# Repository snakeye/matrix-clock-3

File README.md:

# LED Matrix Clock v3

## Overview
Imagine combining the charm of retro LED displays with modern smart technology. **LED Matrix Clock v3** is a creative DIY project that transforms five 8x8 LED matrices into a sleek timepiece. Powered by an ESP8266 microcontroller, this clock not only displays the current time but also keeps it accurate by syncing with an NTP server. The DS3231 RTC module ensures reliability, while automatic daylight saving adjustments make it smarter than your average clock. Built using the Arduino framework and developed in the PlatformIO environment, this project is a perfect blend of classic aesthetics and cutting-edge convenience.

## Features
- **Time Display**: Shows the current time in the local time zone.
- **Automatic Daylight Calculation**: Adjusts for daylight saving time automatically.
- **NTP Synchronization**: Regular updates to the RTC clock via NTP ensure time accuracy.
- **Automatic Brightness**: The display brightness is adjusted according to ambient lighting.

## Hardware Requirements
- **ESP8266 (ESP-12 Module)**
- **5 x 8x8 LED Matrices using MAX7219 drivers**
- **DS3231 RTC Module**

## Software Requirements
- **PlatformIO** (installed via Python Pipenv)
- **Arduino Framework**
- **Python 3.x**

## Installation Instructions

### 1. Clone the Repository
```bash
git clone https://github.com/snakeye/matrix-clock-3.git
cd matrix-clock-3
```

### 3. Set Up the Environment
Ensure you have **Python 3.x** installed. Use Pipenv to install PlatformIO and set up the environment:
```bash
pip install pipenv
pipenv install --dev
pipenv shell
```
This command will install PlatformIO and any additional dependencies needed for the project.

### 2. Configure WiFi Connection
Before building the firmware, set up your WiFi connection:
1. Locate the file `src/config.cpp.example` in the repository.
2. Rename the file to `src/config.cpp`:
   ```bash
   mv src/config.cpp.example src/config.cpp
   ```
3. Open `src/config.cpp` in a text editor and update the placeholders with your WiFi network name (SSID) and password:
   ```cpp
   const char* ssid = "YourNetworkName";
   const char* password = "YourNetworkPassword";
   ```

### 4. Build the Firmware
Use the following command within the Pipenv shell to build the firmware:
```bash
platformio run
```

### 5. Upload the Firmware
Ensure your ESP8266 is connected via USB, and upload the firmware using:
```bash
platformio run --target upload
```
Following updates can be performed using OTA. Discover devices' IP address and run the following command:
```bash
platformio run --target upload --upload-port 192.168.1.179
```

## Usage
Once the firmware is uploaded, the clock will start running and display the current time. It will automatically adjust for daylight saving time and periodically synchronize with an NTP server.

## Troubleshooting
- Ensure your ESP8266 module is properly connected and powered.
- If the upload fails, check the USB connection and the selected upload port in `platformio.ini`.
- Verify your Wi-Fi credentials are correctly configured in the `src/config.cpp` file.

## License
This project is licensed under the MIT License. See the LICENSE file for more details.

## Contributions
Contributions are welcome! Please fork the repository and create a pull request with your improvements or fixes.

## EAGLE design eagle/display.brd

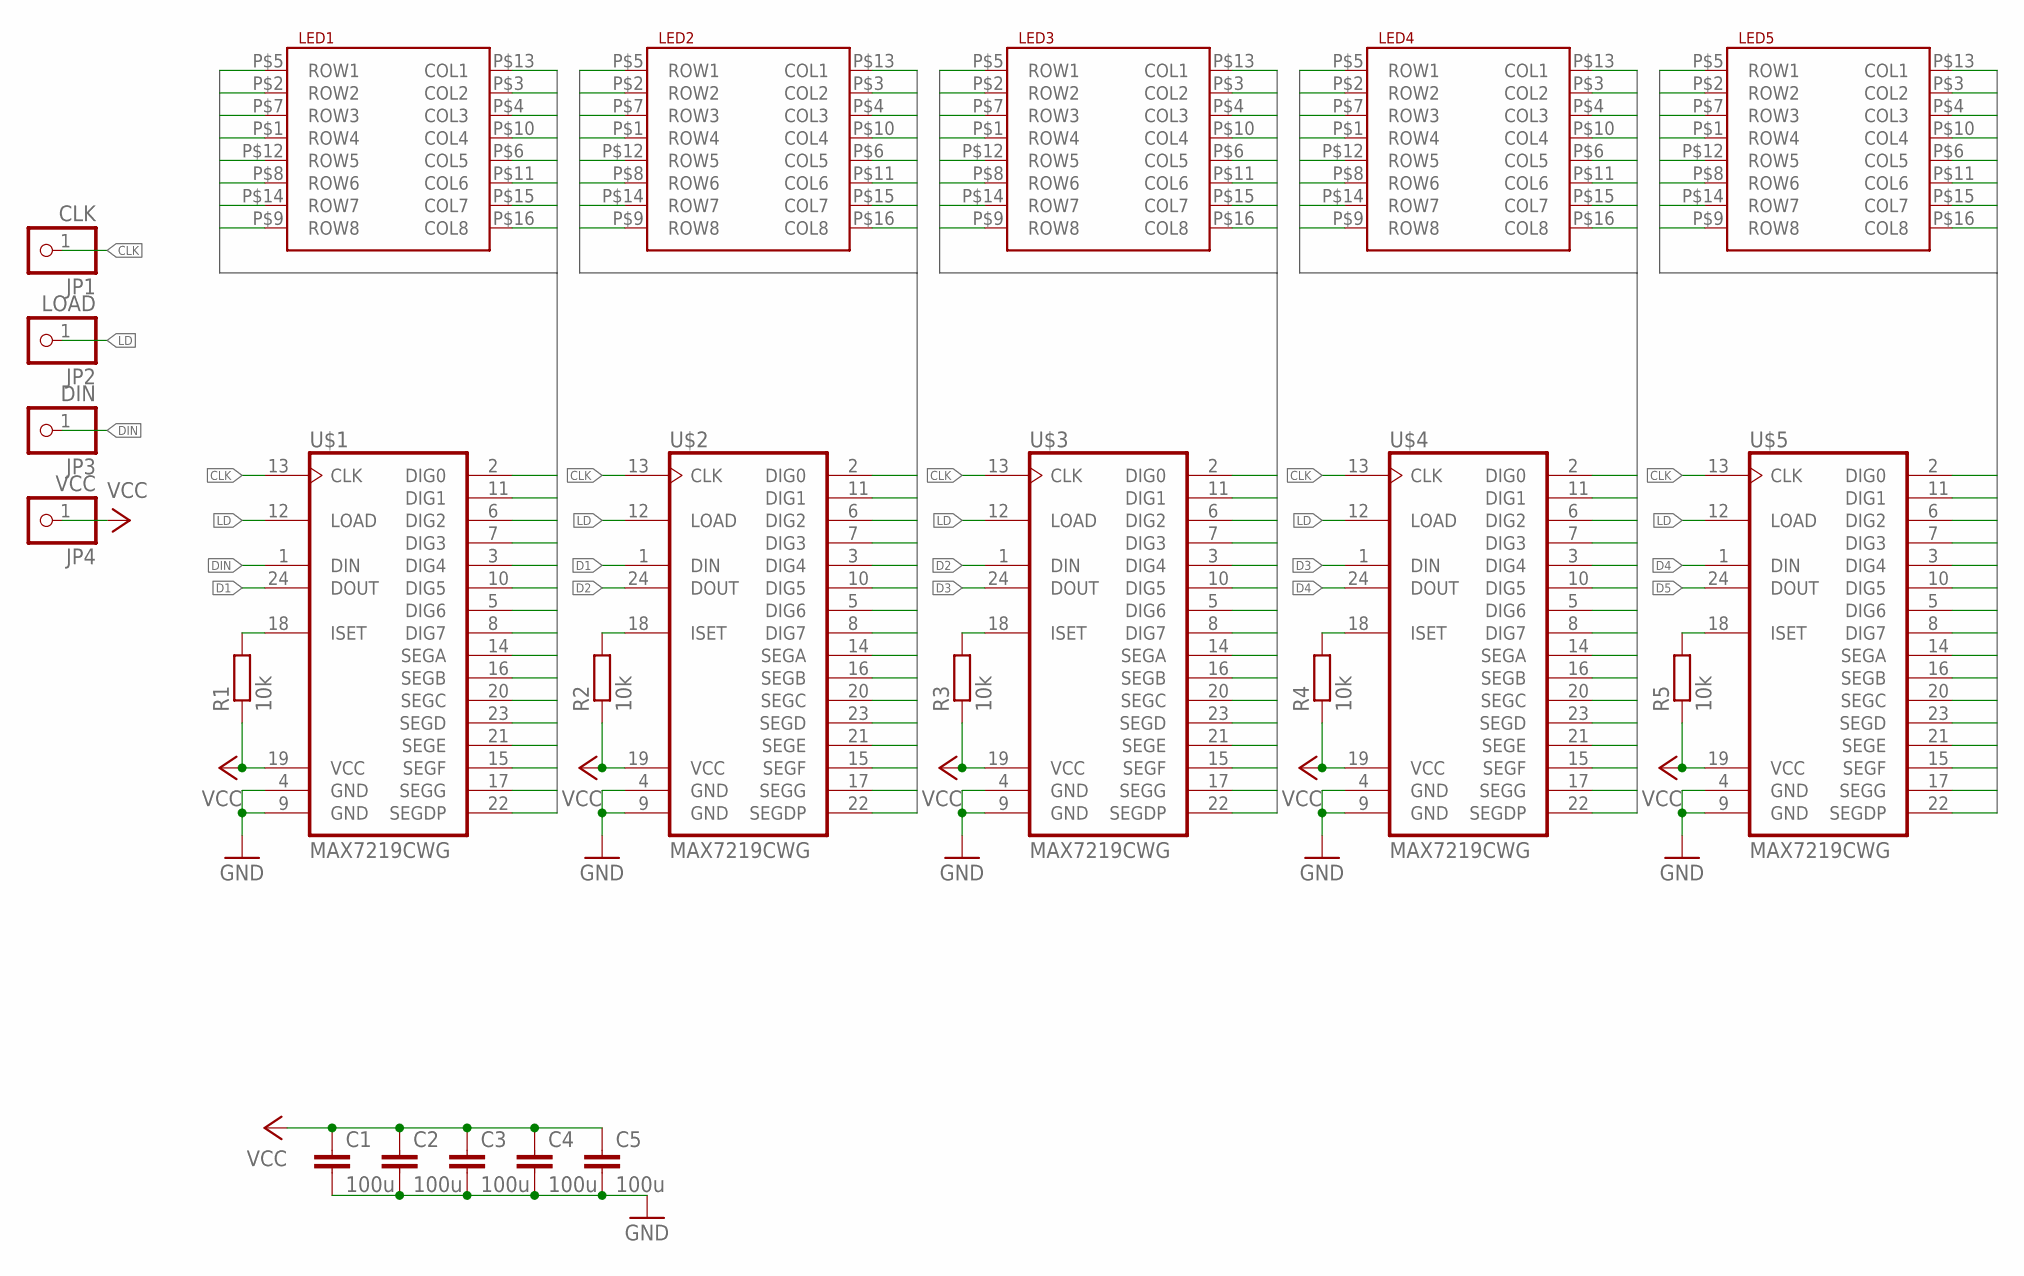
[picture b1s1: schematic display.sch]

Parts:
C1, C2, C3, C4, C5: 100u; C0805
JP1: CLK; 1X01
JP2: LOAD; 1X01
JP3: DIN; 1X01
JP4: VCC; 1X01
LED1, LED2, LED3, LED4, LED5: LED_8X8_MATRIX07088BH; MATRIX_8X8_20MM
R1, R2, R3, R4, R5: 10k; R0805
U$1, U$2, U$3, U$4, U$5: MAX7219CWG; SO24L

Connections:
CLK: JP1.1, U$1.13 (CLK), U$2.13 (CLK), U$3.13 (CLK), U$4.13 (CLK), U$5.13 (CLK)
D1: U$1.24 (DOUT), U$2.1 (DIN)
D2: U$2.24 (DOUT), U$3.1 (DIN)
D3: U$3.24 (DOUT), U$4.1 (DIN)
D4: U$4.24 (DOUT), U$5.1 (DIN)
D5: U$5.24 (DOUT)
DIN: JP3.1, U$1.1 (DIN)
GND: C1.2, C2.2, C3.2, C4.2, C5.2, U$1.4 (GND), U$1.9 (GND), U$2.4 (GND), U$2.9 (GND), U$3.4 (GND), U$3.9 (GND), U$4.4 (GND), U$4.9 (GND), U$5.4 (GND), U$5.9 (GND)
LD: JP2.1, U$1.12 (LOAD), U$2.12 (LOAD), U$3.12 (LOAD), U$4.12 (LOAD), U$5.12 (LOAD)
MATRIX1_ANODE1: LED1.P$5 (ROW1), U$1.14 (SEGA)
MATRIX1_ANODE2: LED1.P$2 (ROW2), U$1.16 (SEGB)
MATRIX1_ANODE3: LED1.P$7 (ROW3), U$1.20 (SEGC)
MATRIX1_ANODE4: LED1.P$1 (ROW4), U$1.23 (SEGD)
MATRIX1_ANODE5: LED1.P$12 (ROW5), U$1.21 (SEGE)
MATRIX1_ANODE6: LED1.P$8 (ROW6), U$1.15 (SEGF)
MATRIX1_ANODE7: LED1.P$14 (ROW7), U$1.17 (SEGG)
MATRIX1_ANODE8: LED1.P$9 (ROW8), U$1.22 (SEGDP)
MATRIX1_CATHODE1: LED1.P$13 (COL1), U$1.2 (DIG0)
MATRIX1_CATHODE2: LED1.P$3 (COL2), U$1.11 (DIG1)
MATRIX1_CATHODE3: LED1.P$4 (COL3), U$1.6 (DIG2)
MATRIX1_CATHODE4: LED1.P$10 (COL4), U$1.7 (DIG3)
MATRIX1_CATHODE5: LED1.P$6 (COL5), U$1.3 (DIG4)
MATRIX1_CATHODE6: LED1.P$11 (COL6), U$1.10 (DIG5)
MATRIX1_CATHODE7: LED1.P$15 (COL7), U$1.5 (DIG6)
MATRIX1_CATHODE8: LED1.P$16 (COL8), U$1.8 (DIG7)
MATRIX2_ANODE1: LED2.P$5 (ROW1), U$2.14 (SEGA)
MATRIX2_ANODE2: LED2.P$2 (ROW2), U$2.16 (SEGB)
MATRIX2_ANODE3: LED2.P$7 (ROW3), U$2.20 (SEGC)
MATRIX2_ANODE4: LED2.P$1 (ROW4), U$2.23 (SEGD)
MATRIX2_ANODE5: LED2.P$12 (ROW5), U$2.21 (SEGE)
MATRIX2_ANODE6: LED2.P$8 (ROW6), U$2.15 (SEGF)
MATRIX2_ANODE7: LED2.P$14 (ROW7), U$2.17 (SEGG)
MATRIX2_ANODE8: LED2.P$9 (ROW8), U$2.22 (SEGDP)
MATRIX2_CATHODE1: LED2.P$13 (COL1), U$2.2 (DIG0)
MATRIX2_CATHODE2: LED2.P$3 (COL2), U$2.11 (DIG1)
MATRIX2_CATHODE3: LED2.P$4 (COL3), U$2.6 (DIG2)
MATRIX2_CATHODE4: LED2.P$10 (COL4), U$2.7 (DIG3)
MATRIX2_CATHODE5: LED2.P$6 (COL5), U$2.3 (DIG4)
MATRIX2_CATHODE6: LED2.P$11 (COL6), U$2.10 (DIG5)
MATRIX2_CATHODE7: LED2.P$15 (COL7), U$2.5 (DIG6)
MATRIX2_CATHODE8: LED2.P$16 (COL8), U$2.8 (DIG7)
MATRIX3_ANODE1: LED3.P$5 (ROW1), U$3.14 (SEGA)
MATRIX3_ANODE2: LED3.P$2 (ROW2), U$3.16 (SEGB)
MATRIX3_ANODE3: LED3.P$7 (ROW3), U$3.20 (SEGC)
MATRIX3_ANODE4: LED3.P$1 (ROW4), U$3.23 (SEGD)
MATRIX3_ANODE5: LED3.P$12 (ROW5), U$3.21 (SEGE)
MATRIX3_ANODE6: LED3.P$8 (ROW6), U$3.15 (SEGF)
MATRIX3_ANODE7: LED3.P$14 (ROW7), U$3.17 (SEGG)
MATRIX3_ANODE8: LED3.P$9 (ROW8), U$3.22 (SEGDP)
MATRIX3_CATHODE1: LED3.P$13 (COL1), U$3.2 (DIG0)
MATRIX3_CATHODE2: LED3.P$3 (COL2), U$3.11 (DIG1)
MATRIX3_CATHODE3: LED3.P$4 (COL3), U$3.6 (DIG2)
MATRIX3_CATHODE4: LED3.P$10 (COL4), U$3.7 (DIG3)
MATRIX3_CATHODE5: LED3.P$6 (COL5), U$3.3 (DIG4)
MATRIX3_CATHODE6: LED3.P$11 (COL6), U$3.10 (DIG5)
MATRIX3_CATHODE7: LED3.P$15 (COL7), U$3.5 (DIG6)
MATRIX3_CATHODE8: LED3.P$16 (COL8), U$3.8 (DIG7)
MATRIX4_ANODE1: LED4.P$5 (ROW1), U$4.14 (SEGA)
MATRIX4_ANODE2: LED4.P$2 (ROW2), U$4.16 (SEGB)
MATRIX4_ANODE3: LED4.P$7 (ROW3), U$4.20 (SEGC)
MATRIX4_ANODE4: LED4.P$1 (ROW4), U$4.23 (SEGD)
MATRIX4_ANODE5: LED4.P$12 (ROW5), U$4.21 (SEGE)
MATRIX4_ANODE6: LED4.P$8 (ROW6), U$4.15 (SEGF)
MATRIX4_ANODE7: LED4.P$14 (ROW7), U$4.17 (SEGG)
MATRIX4_ANODE8: LED4.P$9 (ROW8), U$4.22 (SEGDP)
MATRIX4_CATHODE1: LED4.P$13 (COL1), U$4.2 (DIG0)
MATRIX4_CATHODE2: LED4.P$3 (COL2), U$4.11 (DIG1)
MATRIX4_CATHODE3: LED4.P$4 (COL3), U$4.6 (DIG2)
MATRIX4_CATHODE4: LED4.P$10 (COL4), U$4.7 (DIG3)
MATRIX4_CATHODE5: LED4.P$6 (COL5), U$4.3 (DIG4)
MATRIX4_CATHODE6: LED4.P$11 (COL6), U$4.10 (DIG5)
MATRIX4_CATHODE7: LED4.P$15 (COL7), U$4.5 (DIG6)
MATRIX4_CATHODE8: LED4.P$16 (COL8), U$4.8 (DIG7)
MATRIX5_ANODE1: LED5.P$5 (ROW1), U$5.14 (SEGA)
MATRIX5_ANODE2: LED5.P$2 (ROW2), U$5.16 (SEGB)
MATRIX5_ANODE3: LED5.P$7 (ROW3), U$5.20 (SEGC)
MATRIX5_ANODE4: LED5.P$1 (ROW4), U$5.23 (SEGD)
MATRIX5_ANODE5: LED5.P$12 (ROW5), U$5.21 (SEGE)
MATRIX5_ANODE6: LED5.P$8 (ROW6), U$5.15 (SEGF)
MATRIX5_ANODE7: LED5.P$14 (ROW7), U$5.17 (SEGG)
MATRIX5_ANODE8: LED5.P$9 (ROW8), U$5.22 (SEGDP)
MATRIX5_CATHODE1: LED5.P$13 (COL1), U$5.2 (DIG0)
MATRIX5_CATHODE2: LED5.P$3 (COL2), U$5.11 (DIG1)
MATRIX5_CATHODE3: LED5.P$4 (COL3), U$5.6 (DIG2)
MATRIX5_CATHODE4: LED5.P$10 (COL4), U$5.7 (DIG3)
MATRIX5_CATHODE5: LED5.P$6 (COL5), U$5.3 (DIG4)
MATRIX5_CATHODE6: LED5.P$11 (COL6), U$5.10 (DIG5)
MATRIX5_CATHODE7: LED5.P$15 (COL7), U$5.5 (DIG6)
MATRIX5_CATHODE8: LED5.P$16 (COL8), U$5.8 (DIG7)
unnamed: R5.2, U$5.18 (ISET)
unnamed: R1.2, U$1.18 (ISET)
unnamed: R2.2, U$2.18 (ISET)
unnamed: R3.2, U$3.18 (ISET)
unnamed: R4.2, U$4.18 (ISET)
VCC: C1.1, C2.1, C3.1, C4.1, C5.1, JP4.1, R1.1, R2.1, R3.1, R4.1, R5.1, U$1.19 (VCC), U$2.19 (VCC), U$3.19 (VCC), U$4.19 (VCC), U$5.19 (VCC)

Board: 2 copper layers, 24 parts (15 on the bottom side), 94 nets, no tracks yet.

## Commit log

2018-10-25 Added Eagle files
2018-10-26 removed pinhead
2018-11-03 display board
2019-04-22 create platformio project
2019-05-17 display time from RTC
2019-05-18 ntp time, rtc
2019-05-19 Updated WiFi config
2019-05-19 better display
2023-12-15 Add renovate.json
2024-12-22 Code refactoring
2024-12-22 Bump starlette from 0.39.2 to 0.40.0
    Bumps [starlette](https://github.com/encode/starlette) from 0.39.2 to 0.40.0.
    - [Release notes](https://github.com/encode/starlette/releases)
    - [Changelog](https://github.com/encode/starlette/blob/master/docs/release-notes.md)
    - [Commits](https://github.com/encode/starlette/compare/0.39.2...0.40.0)
    ---
    updated-dependencies:
2024-12-23 Time change animation
2024-12-24 Added button, Added display modes
2024-12-25 Return to short time after 15s
2025-05-04 KiCad project files
2025-05-04 Eagle deleted
2025-06-10 Bump requests from 2.32.3 to 2.32.4
    Bumps [requests](https://github.com/psf/requests) from 2.32.3 to 2.32.4.
    - [Release notes](https://github.com/psf/requests/releases)
    - [Changelog](https://github.com/psf/requests/blob/main/HISTORY.md)
    - [Commits](https://github.com/psf/requests/compare/v2.32.3...v2.32.4)
    ---
    updated-dependencies:
2025-06-19 Bump urllib3 from 2.3.0 to 2.5.0
    Bumps [urllib3](https://github.com/urllib3/urllib3) from 2.3.0 to 2.5.0.
    - [Release notes](https://github.com/urllib3/urllib3/releases)
    - [Changelog](https://github.com/urllib3/urllib3/blob/main/CHANGES.rst)
    - [Commits](https://github.com/urllib3/urllib3/compare/2.3.0...2.5.0)
    ---
    updated-dependencies:
2025-10-28 Bump starlette from 0.39.2 to 0.49.1
    Bumps [starlette](https://github.com/Kludex/starlette) from 0.39.2 to 0.49.1.
    - [Release notes](https://github.com/Kludex/starlette/releases)
    - [Changelog](https://github.com/Kludex/starlette/blob/main/docs/release-notes.md)
    - [Commits](https://github.com/Kludex/starlette/compare/0.39.2...0.49.1)
    ---
    updated-dependencies:
2025-12-06 Bump urllib3 from 2.3.0 to 2.6.0
    Bumps [urllib3](https://github.com/urllib3/urllib3) from 2.3.0 to 2.6.0.
    - [Release notes](https://github.com/urllib3/urllib3/releases)
    - [Changelog](https://github.com/urllib3/urllib3/blob/main/CHANGES.rst)
    - [Commits](https://github.com/urllib3/urllib3/compare/2.3.0...2.6.0)
    ---
    updated-dependencies:
2025-12-22 Bump marshmallow from 3.23.2 to 3.26.2
    Bumps [marshmallow](https://github.com/marshmallow-code/marshmallow) from 3.23.2 to 3.26.2.
    - [Changelog](https://github.com/marshmallow-code/marshmallow/blob/3.26.2/CHANGELOG.rst)
    - [Commits](https://github.com/marshmallow-code/marshmallow/compare/3.23.2...3.26.2)
    ---
    updated-dependencies:
    - dependency-name: marshmallow
2026-01-08 Bump urllib3 from 2.3.0 to 2.6.3
    Bumps [urllib3](https://github.com/urllib3/urllib3) from 2.3.0 to 2.6.3.
    - [Release notes](https://github.com/urllib3/urllib3/releases)
    - [Changelog](https://github.com/urllib3/urllib3/blob/main/CHANGES.rst)
    - [Commits](https://github.com/urllib3/urllib3/compare/2.3.0...2.6.3)
    ---
    updated-dependencies:
